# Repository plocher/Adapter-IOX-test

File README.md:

# Adapter-IOX-test
## License: CERN Open Hardware Licence v1.2

MRCS IOX-16 Test Fixture 

Active Low LED test jig for debugging IOX outputs

When initially setting up an IOX expander, or debugging an existing installation, it is
useful to be able to see the I/O lines changing.  This board is similar to the CMRI Output Test Card,
but the LEDs are isolated from the I/O lines, allowing them to show the status of both outputs and inputs.

Build with pin headers and you can insert the tester into the machined headers on the IOX or cpNode boards.

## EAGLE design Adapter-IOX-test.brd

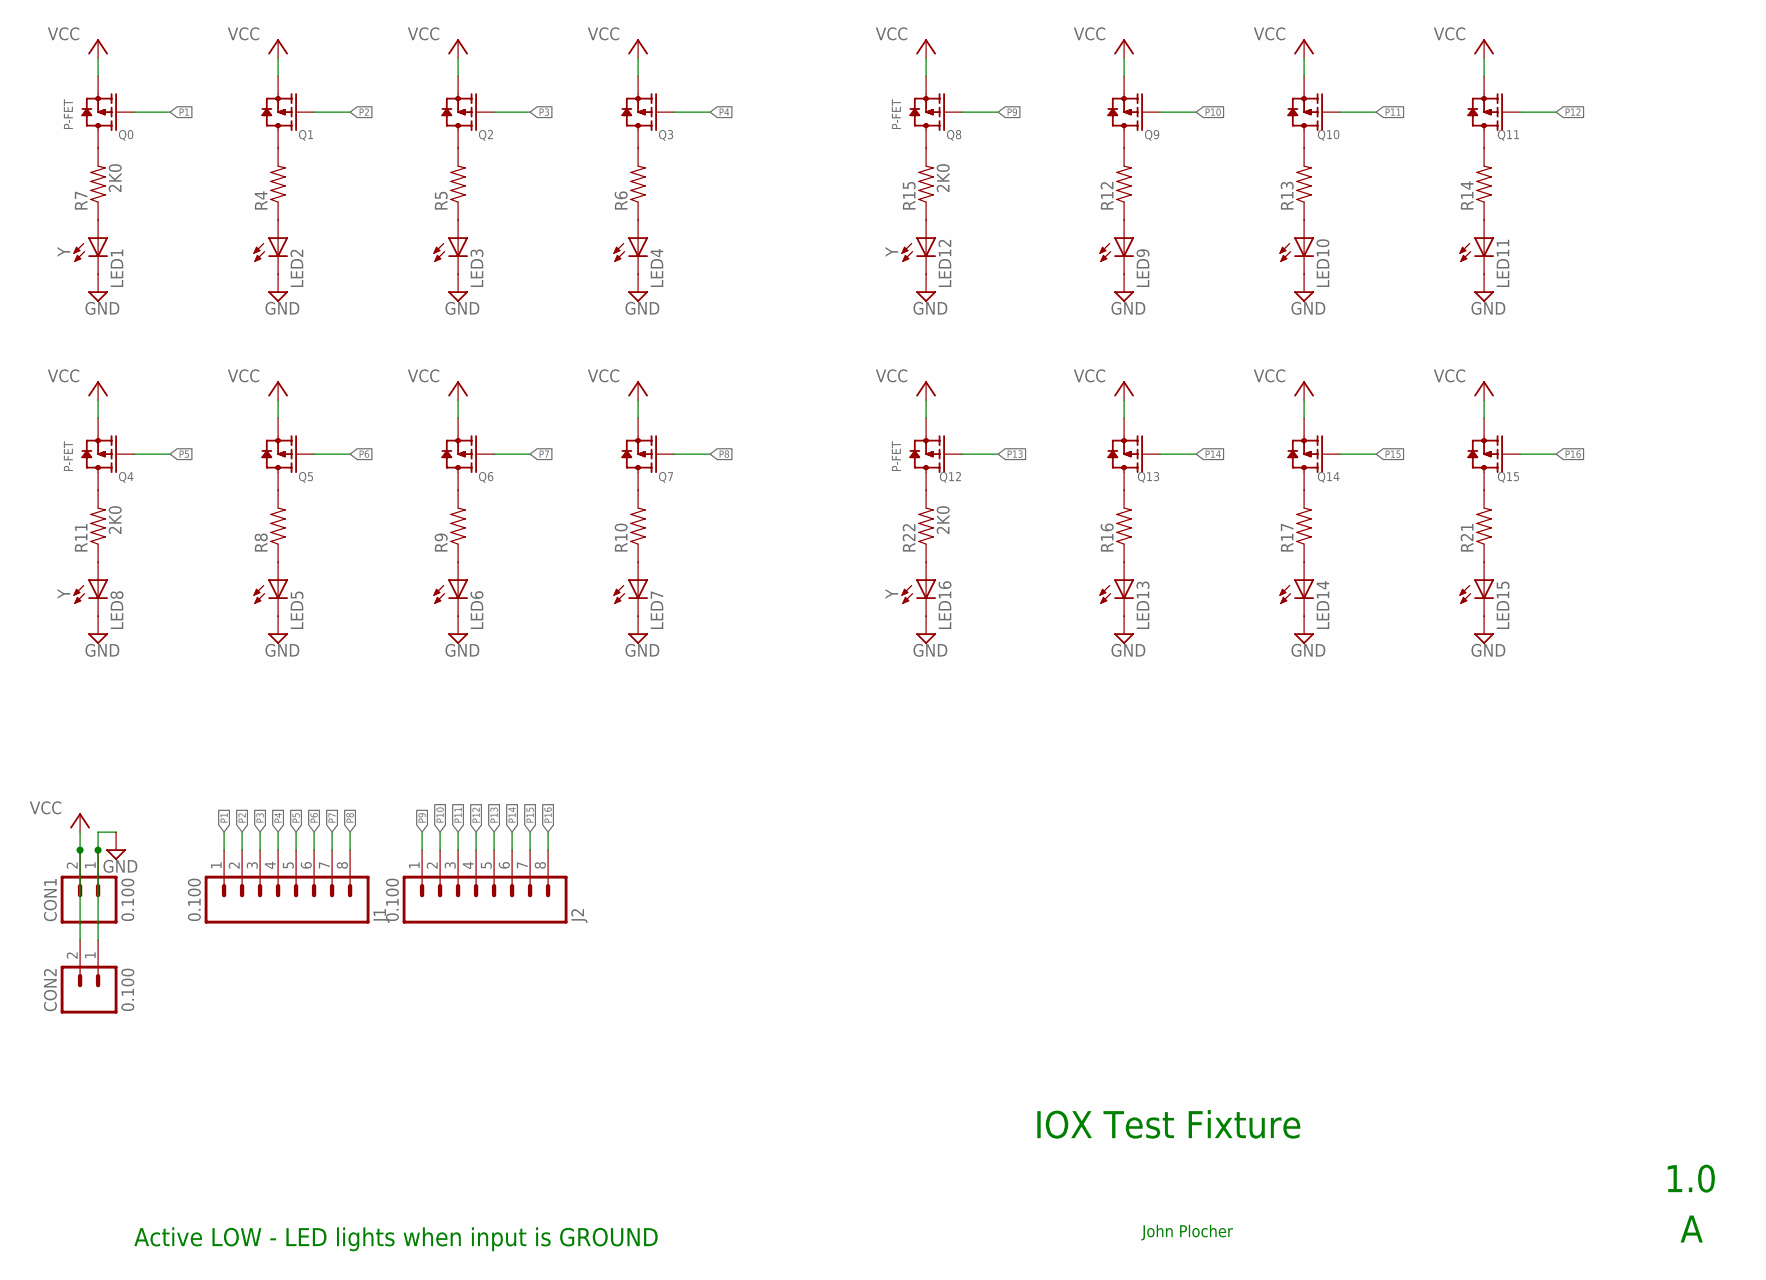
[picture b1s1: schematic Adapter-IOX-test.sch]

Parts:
CON1, CON2: 0.100; 1X02_LOCK
J1, J2: 0.100; 1X08_LOCK
LED1, LED2, LED3, LED4, LED5, LED6, LED7, LED8, LED9, LED10, LED11, LED12, LED13, LED14, LED15, LED16: Y; 0603-LED
Q0, Q1, Q2, Q3, Q4, Q5, Q6, Q7, Q8, Q9, Q10, Q11, Q12, Q13, Q14, Q15: P-FET; SOT23
R4, R5, R6, R7, R8, R9, R10, R11, R12, R13, R14, R15, R16, R17, R21, R22: 2K0; 0805-RES

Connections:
GND: CON1.1 (A), CON2.1 (A), LED1.C, LED2.C, LED3.C, LED4.C, LED5.C, LED6.C, LED7.C, LED8.C, LED9.C, LED10.C, LED11.C, LED12.C, LED13.C, LED14.C, LED15.C, LED16.C
unnamed: Q4.3 (D), R11.2
unnamed: Q5.3 (D), R8.2
unnamed: Q6.3 (D), R9.2
unnamed: Q7.3 (D), R10.2
unnamed: LED8.A, R11.1
unnamed: LED5.A, R8.1
unnamed: LED6.A, R9.1
unnamed: LED7.A, R10.1
unnamed: Q8.3 (D), R15.2
unnamed: Q9.3 (D), R12.2
unnamed: Q10.3 (D), R13.2
unnamed: Q11.3 (D), R14.2
unnamed: LED12.A, R15.1
unnamed: LED9.A, R12.1
unnamed: LED10.A, R13.1
unnamed: LED11.A, R14.1
unnamed: Q12.3 (D), R22.2
unnamed: Q13.3 (D), R16.2
unnamed: Q14.3 (D), R17.2
unnamed: Q15.3 (D), R21.2
unnamed: LED16.A, R22.1
unnamed: LED13.A, R16.1
unnamed: LED14.A, R17.1
unnamed: LED15.A, R21.1
unnamed: Q0.3 (D), R7.2
unnamed: Q1.3 (D), R4.2
unnamed: Q2.3 (D), R5.2
unnamed: Q3.3 (D), R6.2
unnamed: LED1.A, R7.1
unnamed: LED2.A, R4.1
unnamed: LED3.A, R5.1
unnamed: LED4.A, R6.1
P1: J1.1, Q0.1 (G)
P2: J1.2, Q1.1 (G)
P3: J1.3, Q2.1 (G)
P4: J1.4, Q3.1 (G)
P5: J1.5, Q4.1 (G)
P6: J1.6, Q5.1 (G)
P7: J1.7, Q6.1 (G)
P8: J1.8, Q7.1 (G)
P9: J2.1, Q8.1 (G)
P10: J2.2, Q9.1 (G)
P11: J2.3, Q10.1 (G)
P12: J2.4, Q11.1 (G)
P13: J2.5, Q12.1 (G)
P14: J2.6, Q13.1 (G)
P15: J2.7, Q14.1 (G)
P16: J2.8, Q15.1 (G)
VCC: CON1.2 (B), CON2.2 (B), Q0.2 (S), Q1.2 (S), Q2.2 (S), Q3.2 (S), Q4.2 (S), Q5.2 (S), Q6.2 (S), Q7.2 (S), Q8.2 (S), Q9.2 (S), Q10.2 (S), Q11.2 (S), Q12.2 (S), Q13.2 (S), Q14.2 (S), Q15.2 (S)

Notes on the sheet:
IOX Test Fixture
1.0
John Plocher
Active LOW - LED lights when input is GROUND

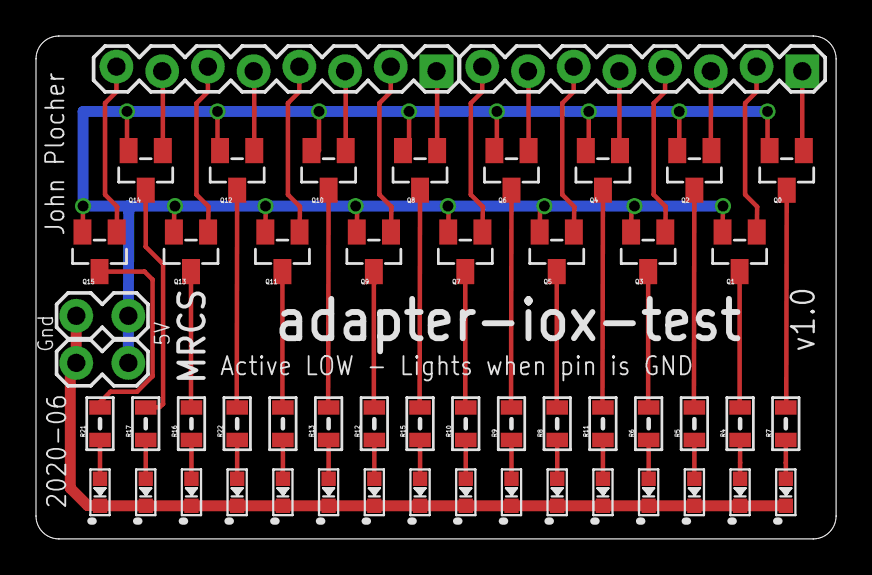
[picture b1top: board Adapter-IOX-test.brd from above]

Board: 2 copper layers, 44.5 x 27.9 mm, 52 parts (0 on the bottom side), 50 nets.

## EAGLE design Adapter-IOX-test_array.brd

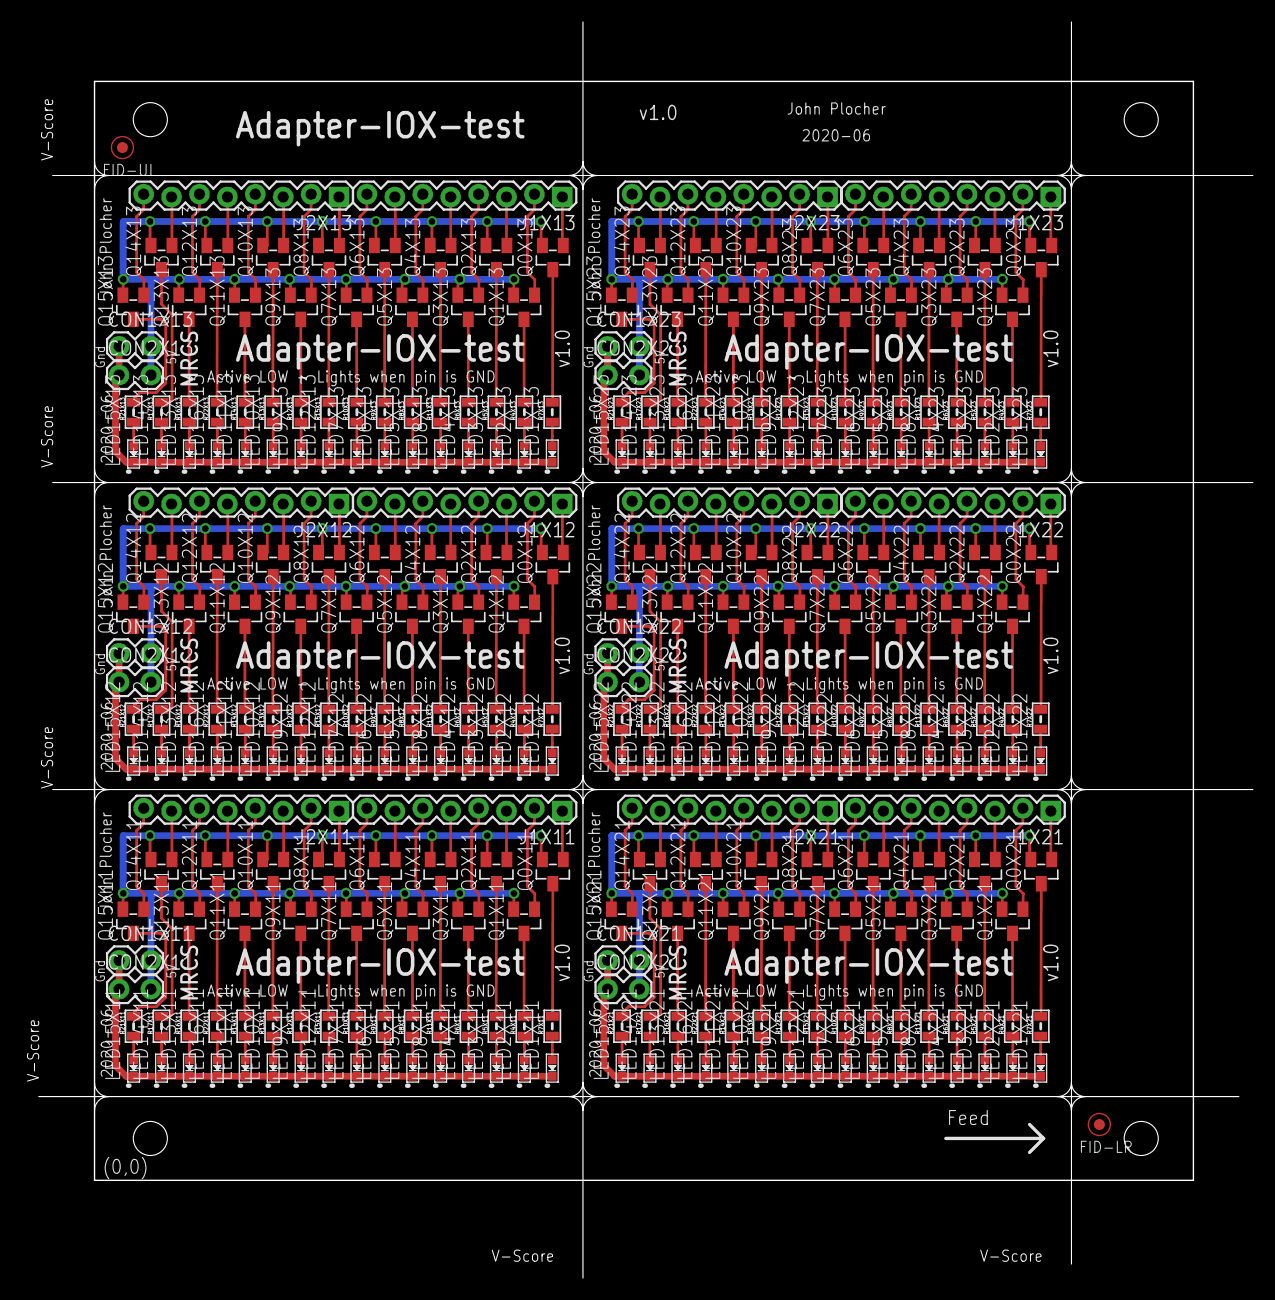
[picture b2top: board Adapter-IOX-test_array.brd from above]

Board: 2 copper layers, 111.9 x 114.2 mm, 315 parts (0 on the bottom side), 300 nets.

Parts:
CON1X11, CON1X12, CON1X13, CON1X21, CON1X22, CON1X23, CON2X11, CON2X12, CON2X13, CON2X21, CON2X22, CON2X23: 0.100; 1X02_LOCK
FID-LR: FIDUCIAL; FIDUCIAL_1MM
FID-UL: FIDUCIAL; FIDUCIAL_1MM
J1X11, J1X12, J1X13, J1X21, J1X22, J1X23, J2X11, J2X12, J2X13, J2X21, J2X22, J2X23: 0.100; 1X08_LOCK
LED1X11, LED1X12, LED1X13, LED1X21, LED1X22, LED1X23, LED2X11, LED2X12, LED2X13, LED2X21, LED2X22, LED2X23, LED3X11, LED3X12, LED3X13, LED3X21, LED3X22, LED3X23, LED4X11, LED4X12, LED4X13, LED4X21, LED4X22, LED4X23, LED5X11, LED5X12, LED5X13, LED5X21, LED5X22, LED5X23, LED6X11, LED6X12, LED6X13, LED6X21, LED6X22, LED6X23, LED7X11, LED7X12, LED7X13, LED7X21, LED7X22, LED7X23, LED8X11, LED8X12, LED8X13, LED8X21, LED8X22, LED8X23, LED9X11, LED9X12, LED9X13, LED9X21, LED9X22, LED9X23, LED10X11, LED10X12, LED10X13, LED10X21, LED10X22, LED10X23, LED11X11, LED11X12, LED11X13, LED11X21, LED11X22, LED11X23, LED12X11, LED12X12, LED12X13, LED12X21, LED12X22, LED12X23, LED13X11, LED13X12, LED13X13, LED13X21, LED13X22, LED13X23, LED14X11, LED14X12, LED14X13, LED14X21, LED14X22, LED14X23, LED15X11, LED15X12, LED15X13, LED15X21, LED15X22, LED15X23, LED16X11, LED16X12, LED16X13, LED16X21, LED16X22, LED16X23: Y; 0603-LED
Q0X11, Q0X12, Q0X13, Q0X21, Q0X22, Q0X23, Q1X11, Q1X12, Q1X13, Q1X21, Q1X22, Q1X23, Q2X11, Q2X12, Q2X13, Q2X21, Q2X22, Q2X23, Q3X11, Q3X12, Q3X13, Q3X21, Q3X22, Q3X23, Q4X11, Q4X12, Q4X13, Q4X21, Q4X22, Q4X23, Q5X11, Q5X12, Q5X13, Q5X21, Q5X22, Q5X23, Q6X11, Q6X12, Q6X13, Q6X21, Q6X22, Q6X23, Q7X11, Q7X12, Q7X13, Q7X21, Q7X22, Q7X23, Q8X11, Q8X12, Q8X13, Q8X21, Q8X22, Q8X23, Q9X11, Q9X12, Q9X13, Q9X21, Q9X22, Q9X23, Q10X11, Q10X12, Q10X13, Q10X21, Q10X22, Q10X23, Q11X11, Q11X12, Q11X13, Q11X21, Q11X22, Q11X23, Q12X11, Q12X12, Q12X13, Q12X21, Q12X22, Q12X23, Q13X11, Q13X12, Q13X13, Q13X21, Q13X22, Q13X23, Q14X11, Q14X12, Q14X13, Q14X21, Q14X22, Q14X23, Q15X11, Q15X12, Q15X13, Q15X21, Q15X22, Q15X23: P-FET; SOT23
R4X11, R4X12, R4X13, R4X21, R4X22, R4X23, R5X11, R5X12, R5X13, R5X21, R5X22, R5X23, R6X11, R6X12, R6X13, R6X21, R6X22, R6X23, R7X11, R7X12, R7X13, R7X21, R7X22, R7X23, R8X11, R8X12, R8X13, R8X21, R8X22, R8X23, R9X11, R9X12, R9X13, R9X21, R9X22, R9X23, R10X11, R10X12, R10X13, R10X21, R10X22, R10X23, R11X11, R11X12, R11X13, R11X21, R11X22, R11X23, R12X11, R12X12, R12X13, R12X21, R12X22, R12X23, R13X11, R13X12, R13X13, R13X21, R13X22, R13X23, R14X11, R14X12, R14X13, R14X21, R14X22, R14X23, R15X11, R15X12, R15X13, R15X21, R15X22, R15X23, R16X11, R16X12, R16X13, R16X21, R16X22, R16X23, R17X11, R17X12, R17X13, R17X21, R17X22, R17X23, R21X11, R21X12, R21X13, R21X21, R21X22, R21X23, R22X11, R22X12, R22X13, R22X21, R22X22, R22X23: 2K0; 0805-RES
R22X1: BOARD; BOARD-10X10-TEMPLATE

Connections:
GNDX11: CON1X11.1, CON2X11.1, LED1X11.C, LED2X11.C, LED3X11.C, LED4X11.C, LED5X11.C, LED6X11.C, LED7X11.C, LED8X11.C, LED9X11.C, LED10X11.C, LED11X11.C, LED12X11.C, LED13X11.C, LED14X11.C, LED15X11.C, LED16X11.C
GNDX12: CON1X12.1, CON2X12.1, LED1X12.C, LED2X12.C, LED3X12.C, LED4X12.C, LED5X12.C, LED6X12.C, LED7X12.C, LED8X12.C, LED9X12.C, LED10X12.C, LED11X12.C, LED12X12.C, LED13X12.C, LED14X12.C, LED15X12.C, LED16X12.C
GNDX13: CON1X13.1, CON2X13.1, LED1X13.C, LED2X13.C, LED3X13.C, LED4X13.C, LED5X13.C, LED6X13.C, LED7X13.C, LED8X13.C, LED9X13.C, LED10X13.C, LED11X13.C, LED12X13.C, LED13X13.C, LED14X13.C, LED15X13.C, LED16X13.C
GNDX21: CON1X21.1, CON2X21.1, LED1X21.C, LED2X21.C, LED3X21.C, LED4X21.C, LED5X21.C, LED6X21.C, LED7X21.C, LED8X21.C, LED9X21.C, LED10X21.C, LED11X21.C, LED12X21.C, LED13X21.C, LED14X21.C, LED15X21.C, LED16X21.C
GNDX22: CON1X22.1, CON2X22.1, LED1X22.C, LED2X22.C, LED3X22.C, LED4X22.C, LED5X22.C, LED6X22.C, LED7X22.C, LED8X22.C, LED9X22.C, LED10X22.C, LED11X22.C, LED12X22.C, LED13X22.C, LED14X22.C, LED15X22.C, LED16X22.C
GNDX23: CON1X23.1, CON2X23.1, LED1X23.C, LED2X23.C, LED3X23.C, LED4X23.C, LED5X23.C, LED6X23.C, LED7X23.C, LED8X23.C, LED9X23.C, LED10X23.C, LED11X23.C, LED12X23.C, LED13X23.C, LED14X23.C, LED15X23.C, LED16X23.C
unnamed: Q4X11.3, R11X11.2
unnamed: Q4X12.3, R11X12.2
unnamed: Q4X13.3, R11X13.2
unnamed: Q4X21.3, R11X21.2
unnamed: Q4X22.3, R11X22.2
unnamed: Q4X23.3, R11X23.2
unnamed: Q5X11.3, R8X11.2
unnamed: Q5X12.3, R8X12.2
unnamed: Q5X13.3, R8X13.2
unnamed: Q5X21.3, R8X21.2
unnamed: Q5X22.3, R8X22.2
unnamed: Q5X23.3, R8X23.2
unnamed: Q6X11.3, R9X11.2
unnamed: Q6X12.3, R9X12.2
unnamed: Q6X13.3, R9X13.2
unnamed: Q6X21.3, R9X21.2
unnamed: Q6X22.3, R9X22.2
unnamed: Q6X23.3, R9X23.2
unnamed: Q7X11.3, R10X11.2
unnamed: Q7X12.3, R10X12.2
unnamed: Q7X13.3, R10X13.2
unnamed: Q7X21.3, R10X21.2
unnamed: Q7X22.3, R10X22.2
unnamed: Q7X23.3, R10X23.2
unnamed: LED8X11.A, R11X11.1
unnamed: LED8X12.A, R11X12.1
unnamed: LED8X13.A, R11X13.1
unnamed: LED8X21.A, R11X21.1
unnamed: LED8X22.A, R11X22.1
unnamed: LED8X23.A, R11X23.1
unnamed: LED5X11.A, R8X11.1
unnamed: LED5X12.A, R8X12.1
unnamed: LED5X13.A, R8X13.1
unnamed: LED5X21.A, R8X21.1
unnamed: LED5X22.A, R8X22.1
unnamed: LED5X23.A, R8X23.1
unnamed: LED6X11.A, R9X11.1
unnamed: LED6X12.A, R9X12.1
unnamed: LED6X13.A, R9X13.1
unnamed: LED6X21.A, R9X21.1
unnamed: LED6X22.A, R9X22.1
unnamed: LED6X23.A, R9X23.1
unnamed: LED7X11.A, R10X11.1
unnamed: LED7X12.A, R10X12.1
unnamed: LED7X13.A, R10X13.1
unnamed: LED7X21.A, R10X21.1
unnamed: LED7X22.A, R10X22.1
unnamed: LED7X23.A, R10X23.1
unnamed: Q8X11.3, R15X11.2
unnamed: Q8X12.3, R15X12.2
unnamed: Q8X13.3, R15X13.2
unnamed: Q8X21.3, R15X21.2
unnamed: Q8X22.3, R15X22.2
unnamed: Q8X23.3, R15X23.2
unnamed: Q9X11.3, R12X11.2
unnamed: Q9X12.3, R12X12.2
unnamed: Q9X13.3, R12X13.2
unnamed: Q9X21.3, R12X21.2
unnamed: Q9X22.3, R12X22.2
unnamed: Q9X23.3, R12X23.2
unnamed: Q10X11.3, R13X11.2
unnamed: Q10X12.3, R13X12.2
unnamed: Q10X13.3, R13X13.2
unnamed: Q10X21.3, R13X21.2
unnamed: Q10X22.3, R13X22.2
unnamed: Q10X23.3, R13X23.2
unnamed: Q11X11.3, R14X11.2
unnamed: Q11X12.3, R14X12.2
unnamed: Q11X13.3, R14X13.2
unnamed: Q11X21.3, R14X21.2
unnamed: Q11X22.3, R14X22.2
unnamed: Q11X23.3, R14X23.2
unnamed: LED12X11.A, R15X11.1
unnamed: LED12X12.A, R15X12.1
unnamed: LED12X13.A, R15X13.1
unnamed: LED12X21.A, R15X21.1
unnamed: LED12X22.A, R15X22.1
unnamed: LED12X23.A, R15X23.1
unnamed: LED9X11.A, R12X11.1
unnamed: LED9X12.A, R12X12.1
unnamed: LED9X13.A, R12X13.1
unnamed: LED9X21.A, R12X21.1
unnamed: LED9X22.A, R12X22.1
unnamed: LED9X23.A, R12X23.1
unnamed: LED10X11.A, R13X11.1
unnamed: LED10X12.A, R13X12.1
unnamed: LED10X13.A, R13X13.1
unnamed: LED10X21.A, R13X21.1
unnamed: LED10X22.A, R13X22.1
unnamed: LED10X23.A, R13X23.1
unnamed: LED11X11.A, R14X11.1
unnamed: LED11X12.A, R14X12.1
unnamed: LED11X13.A, R14X13.1
unnamed: LED11X21.A, R14X21.1
unnamed: LED11X22.A, R14X22.1
unnamed: LED11X23.A, R14X23.1
unnamed: Q12X11.3, R22X11.2
unnamed: Q12X12.3, R22X12.2
unnamed: Q12X13.3, R22X13.2
unnamed: Q12X21.3, R22X21.2
unnamed: Q12X22.3, R22X22.2
unnamed: Q12X23.3, R22X23.2
unnamed: Q13X11.3, R16X11.2
unnamed: Q13X12.3, R16X12.2
unnamed: Q13X13.3, R16X13.2
unnamed: Q13X21.3, R16X21.2
unnamed: Q13X22.3, R16X22.2
unnamed: Q13X23.3, R16X23.2
unnamed: Q14X11.3, R17X11.2
unnamed: Q14X12.3, R17X12.2
unnamed: Q14X13.3, R17X13.2
unnamed: Q14X21.3, R17X21.2
unnamed: Q14X22.3, R17X22.2
unnamed: Q14X23.3, R17X23.2
unnamed: Q15X11.3, R21X11.2
unnamed: Q15X12.3, R21X12.2
unnamed: Q15X13.3, R21X13.2
unnamed: Q15X21.3, R21X21.2
unnamed: Q15X22.3, R21X22.2
unnamed: Q15X23.3, R21X23.2
unnamed: LED16X11.A, R22X11.1
unnamed: LED16X12.A, R22X12.1
unnamed: LED16X13.A, R22X13.1
unnamed: LED16X21.A, R22X21.1
unnamed: LED16X22.A, R22X22.1
unnamed: LED16X23.A, R22X23.1
unnamed: LED13X11.A, R16X11.1
unnamed: LED13X12.A, R16X12.1
unnamed: LED13X13.A, R16X13.1
unnamed: LED13X21.A, R16X21.1
unnamed: LED13X22.A, R16X22.1
unnamed: LED13X23.A, R16X23.1
unnamed: LED14X11.A, R17X11.1
unnamed: LED14X12.A, R17X12.1
unnamed: LED14X13.A, R17X13.1
unnamed: LED14X21.A, R17X21.1
unnamed: LED14X22.A, R17X22.1
unnamed: LED14X23.A, R17X23.1
unnamed: LED15X11.A, R21X11.1
unnamed: LED15X12.A, R21X12.1
unnamed: LED15X13.A, R21X13.1
unnamed: LED15X21.A, R21X21.1
unnamed: LED15X22.A, R21X22.1
unnamed: LED15X23.A, R21X23.1
unnamed: Q0X11.3, R7X11.2
unnamed: Q0X12.3, R7X12.2
unnamed: Q0X13.3, R7X13.2
unnamed: Q0X21.3, R7X21.2
unnamed: Q0X22.3, R7X22.2
unnamed: Q0X23.3, R7X23.2
unnamed: Q1X11.3, R4X11.2
unnamed: Q1X12.3, R4X12.2
unnamed: Q1X13.3, R4X13.2
unnamed: Q1X21.3, R4X21.2
unnamed: Q1X22.3, R4X22.2
unnamed: Q1X23.3, R4X23.2
unnamed: Q2X11.3, R5X11.2
unnamed: Q2X12.3, R5X12.2
unnamed: Q2X13.3, R5X13.2
unnamed: Q2X21.3, R5X21.2
unnamed: Q2X22.3, R5X22.2
unnamed: Q2X23.3, R5X23.2
unnamed: Q3X11.3, R6X11.2
unnamed: Q3X12.3, R6X12.2
unnamed: Q3X13.3, R6X13.2
unnamed: Q3X21.3, R6X21.2
unnamed: Q3X22.3, R6X22.2
unnamed: Q3X23.3, R6X23.2
unnamed: LED1X11.A, R7X11.1
unnamed: LED1X12.A, R7X12.1
unnamed: LED1X13.A, R7X13.1
unnamed: LED1X21.A, R7X21.1
unnamed: LED1X22.A, R7X22.1
unnamed: LED1X23.A, R7X23.1
unnamed: LED2X11.A, R4X11.1
unnamed: LED2X12.A, R4X12.1
unnamed: LED2X13.A, R4X13.1
unnamed: LED2X21.A, R4X21.1
unnamed: LED2X22.A, R4X22.1
unnamed: LED2X23.A, R4X23.1
unnamed: LED3X11.A, R5X11.1
unnamed: LED3X12.A, R5X12.1
unnamed: LED3X13.A, R5X13.1
unnamed: LED3X21.A, R5X21.1
unnamed: LED3X22.A, R5X22.1
unnamed: LED3X23.A, R5X23.1
unnamed: LED4X11.A, R6X11.1
unnamed: LED4X12.A, R6X12.1
unnamed: LED4X13.A, R6X13.1
unnamed: LED4X21.A, R6X21.1
unnamed: LED4X22.A, R6X22.1
unnamed: LED4X23.A, R6X23.1
P1X11: J1X11.1, Q0X11.1
P1X12: J1X12.1, Q0X12.1
P1X13: J1X13.1, Q0X13.1
P1X21: J1X21.1, Q0X21.1
P1X22: J1X22.1, Q0X22.1
P1X23: J1X23.1, Q0X23.1
P2X11: J1X11.2, Q1X11.1
P2X12: J1X12.2, Q1X12.1
P2X13: J1X13.2, Q1X13.1
P2X21: J1X21.2, Q1X21.1
P2X22: J1X22.2, Q1X22.1
P2X23: J1X23.2, Q1X23.1
P3X11: J1X11.3, Q2X11.1
P3X12: J1X12.3, Q2X12.1
P3X13: J1X13.3, Q2X13.1
P3X21: J1X21.3, Q2X21.1
P3X22: J1X22.3, Q2X22.1
P3X23: J1X23.3, Q2X23.1
P4X11: J1X11.4, Q3X11.1
P4X12: J1X12.4, Q3X12.1
P4X13: J1X13.4, Q3X13.1
P4X21: J1X21.4, Q3X21.1
P4X22: J1X22.4, Q3X22.1
P4X23: J1X23.4, Q3X23.1
P5X11: J1X11.5, Q4X11.1
P5X12: J1X12.5, Q4X12.1
P5X13: J1X13.5, Q4X13.1
P5X21: J1X21.5, Q4X21.1
P5X22: J1X22.5, Q4X22.1
P5X23: J1X23.5, Q4X23.1
P6X11: J1X11.6, Q5X11.1
P6X12: J1X12.6, Q5X12.1
P6X13: J1X13.6, Q5X13.1
P6X21: J1X21.6, Q5X21.1
P6X22: J1X22.6, Q5X22.1
P6X23: J1X23.6, Q5X23.1
P7X11: J1X11.7, Q6X11.1
P7X12: J1X12.7, Q6X12.1
P7X13: J1X13.7, Q6X13.1
P7X21: J1X21.7, Q6X21.1
P7X22: J1X22.7, Q6X22.1
P7X23: J1X23.7, Q6X23.1
P8X11: J1X11.8, Q7X11.1
P8X12: J1X12.8, Q7X12.1
P8X13: J1X13.8, Q7X13.1
P8X21: J1X21.8, Q7X21.1
P8X22: J1X22.8, Q7X22.1
P8X23: J1X23.8, Q7X23.1
P9X11: J2X11.1, Q8X11.1
P9X12: J2X12.1, Q8X12.1
P9X13: J2X13.1, Q8X13.1
P9X21: J2X21.1, Q8X21.1
P9X22: J2X22.1, Q8X22.1
P9X23: J2X23.1, Q8X23.1
P10X11: J2X11.2, Q9X11.1
P10X12: J2X12.2, Q9X12.1
P10X13: J2X13.2, Q9X13.1
P10X21: J2X21.2, Q9X21.1
P10X22: J2X22.2, Q9X22.1
P10X23: J2X23.2, Q9X23.1
P11X11: J2X11.3, Q10X11.1
P11X12: J2X12.3, Q10X12.1
P11X13: J2X13.3, Q10X13.1
P11X21: J2X21.3, Q10X21.1
P11X22: J2X22.3, Q10X22.1
P11X23: J2X23.3, Q10X23.1
P12X11: J2X11.4, Q11X11.1
P12X12: J2X12.4, Q11X12.1
P12X13: J2X13.4, Q11X13.1
P12X21: J2X21.4, Q11X21.1
P12X22: J2X22.4, Q11X22.1
P12X23: J2X23.4, Q11X23.1
P13X11: J2X11.5, Q12X11.1
P13X12: J2X12.5, Q12X12.1
P13X13: J2X13.5, Q12X13.1
P13X21: J2X21.5, Q12X21.1
P13X22: J2X22.5, Q12X22.1
P13X23: J2X23.5, Q12X23.1
P14X11: J2X11.6, Q13X11.1
P14X12: J2X12.6, Q13X12.1
P14X13: J2X13.6, Q13X13.1
P14X21: J2X21.6, Q13X21.1
P14X22: J2X22.6, Q13X22.1
P14X23: J2X23.6, Q13X23.1
P15X11: J2X11.7, Q14X11.1
P15X12: J2X12.7, Q14X12.1
P15X13: J2X13.7, Q14X13.1
P15X21: J2X21.7, Q14X21.1
P15X22: J2X22.7, Q14X22.1
P15X23: J2X23.7, Q14X23.1
P16X11: J2X11.8, Q15X11.1
P16X12: J2X12.8, Q15X12.1
P16X13: J2X13.8, Q15X13.1
P16X21: J2X21.8, Q15X21.1
P16X22: J2X22.8, Q15X22.1
P16X23: J2X23.8, Q15X23.1
VCCX11: CON1X11.2, CON2X11.2, Q0X11.2, Q1X11.2, Q2X11.2, Q3X11.2, Q4X11.2, Q5X11.2, Q6X11.2, Q7X11.2, Q8X11.2, Q9X11.2, Q10X11.2, Q11X11.2, Q12X11.2, Q13X11.2, Q14X11.2, Q15X11.2
VCCX12: CON1X12.2, CON2X12.2, Q0X12.2, Q1X12.2, Q2X12.2, Q3X12.2, Q4X12.2, Q5X12.2, Q6X12.2, Q7X12.2, Q8X12.2, Q9X12.2, Q10X12.2, Q11X12.2, Q12X12.2, Q13X12.2, Q14X12.2, Q15X12.2
VCCX13: CON1X13.2, CON2X13.2, Q0X13.2, Q1X13.2, Q2X13.2, Q3X13.2, Q4X13.2, Q5X13.2, Q6X13.2, Q7X13.2, Q8X13.2, Q9X13.2, Q10X13.2, Q11X13.2, Q12X13.2, Q13X13.2, Q14X13.2, Q15X13.2
VCCX21: CON1X21.2, CON2X21.2, Q0X21.2, Q1X21.2, Q2X21.2, Q3X21.2, Q4X21.2, Q5X21.2, Q6X21.2, Q7X21.2, Q8X21.2, Q9X21.2, Q10X21.2, Q11X21.2, Q12X21.2, Q13X21.2, Q14X21.2, Q15X21.2
VCCX22: CON1X22.2, CON2X22.2, Q0X22.2, Q1X22.2, Q2X22.2, Q3X22.2, Q4X22.2, Q5X22.2, Q6X22.2, Q7X22.2, Q8X22.2, Q9X22.2, Q10X22.2, Q11X22.2, Q12X22.2, Q13X22.2, Q14X22.2, Q15X22.2
VCCX23: CON1X23.2, CON2X23.2, Q0X23.2, Q1X23.2, Q2X23.2, Q3X23.2, Q4X23.2, Q5X23.2, Q6X23.2, Q7X23.2, Q8X23.2, Q9X23.2, Q10X23.2, Q11X23.2, Q12X23.2, Q13X23.2, Q14X23.2, Q15X23.2

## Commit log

2020-06-16 Initial version
2020-06-19 higher density, narrow the board so 2x work with IOX-32
2020-06-20 updated docs
2020-08-05 fixed SPCoast lbr part orientation
2020-10-05 added values for connectors
2020-10-06 normalized values
